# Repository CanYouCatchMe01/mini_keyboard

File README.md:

# Mini keyboard
I'm using this libray for the [Arduino Joystick Library](https://github.com/MHeironimus/ArduinoJoystickLibrary)
to emulate an controller. Then to emulate an XBOX 360 controller I use the [x360ce](https://github.com/x360ce/x360ce) application.

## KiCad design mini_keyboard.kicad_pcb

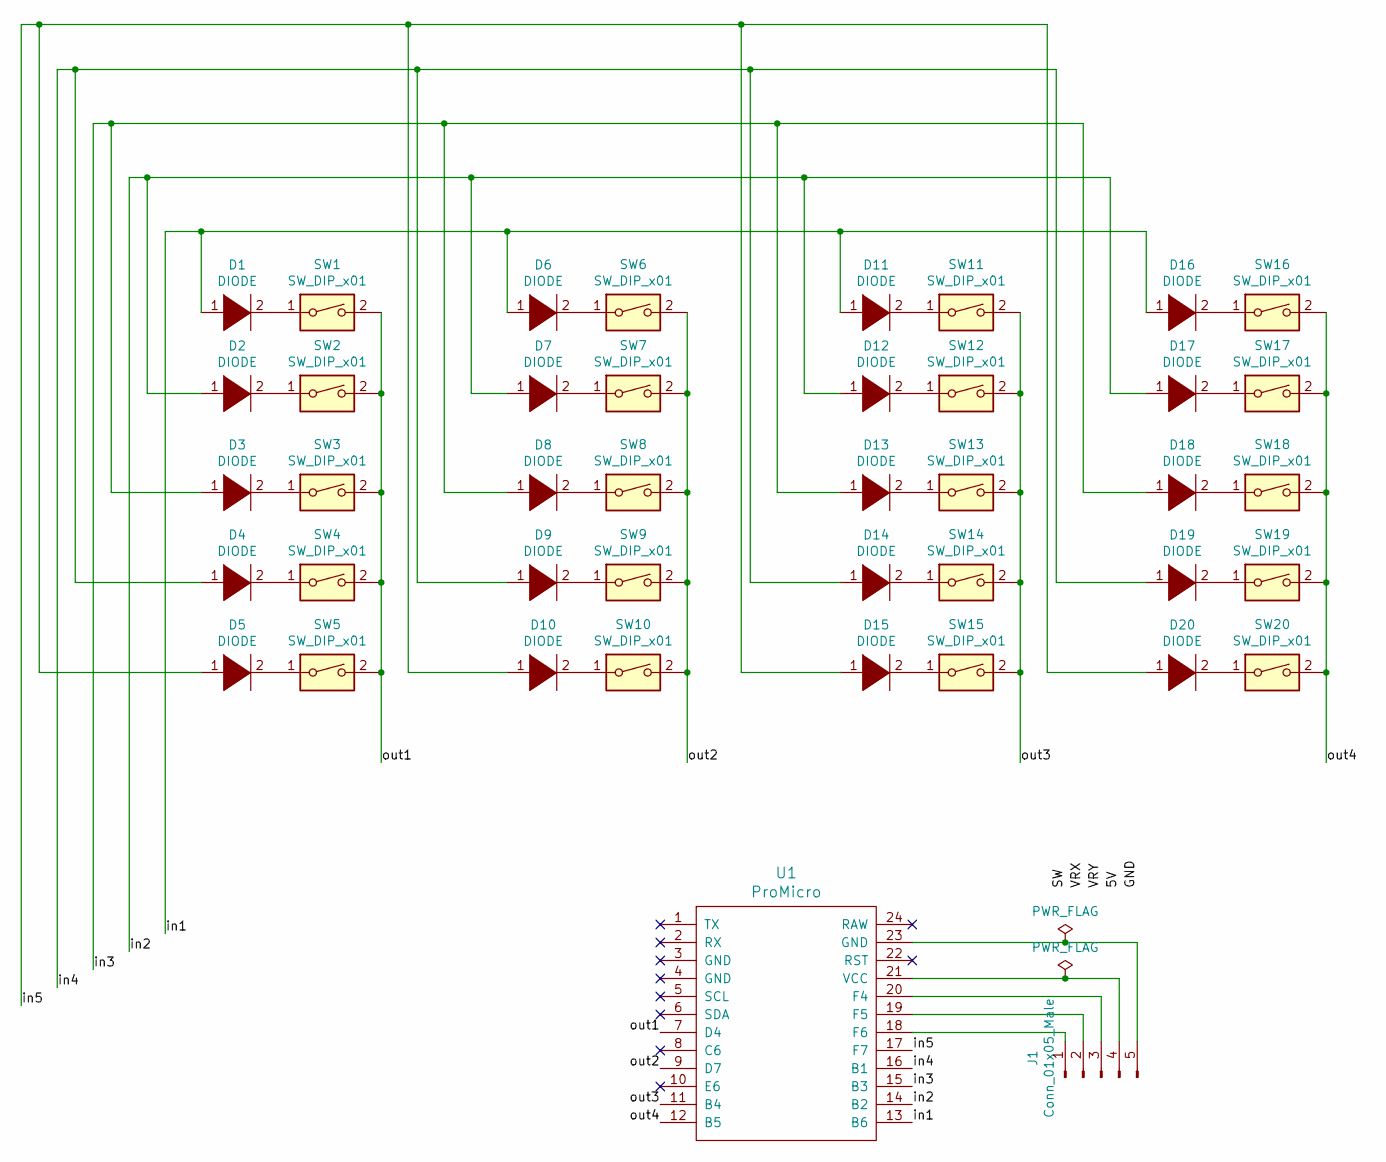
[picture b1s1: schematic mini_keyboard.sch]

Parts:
D1, D2, D3, D4, D5, D6, D7, D8, D9, D10, D11, D12, D13, D14, D15, D16, D17, D18, D19, D20: DIODE; D_T-1_P5.08mm_Horizontal
J1: Conn_01x05_Male; PinHeader_1x05_P2.54mm_Vertical
SW1, SW2, SW3, SW4, SW5, SW6, SW7, SW8, SW9, SW10, SW11, SW12, SW13, SW14, SW15, SW16, SW17, SW18, SW19, SW20: SW_DIP_x01; SW_Cherry_MX_1.00u_Plate
U1: ProMicro

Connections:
/in1: D1.1 (K), D6.1 (K), D11.1 (K), D16.1 (K), U1.13 (B6)
/in2: D2.1 (K), D7.1 (K), D12.1 (K), D17.1 (K), U1.14 (B2)
/in3: D3.1 (K), D8.1 (K), D13.1 (K), D18.1 (K), U1.15 (B3)
/in4: D4.1 (K), D9.1 (K), D14.1 (K), D19.1 (K), U1.16 (B1)
/in5: D5.1 (K), D10.1 (K), D15.1 (K), D20.1 (K), U1.17 (F7)
/out1: SW1.2, SW2.2, SW3.2, SW4.2, SW5.2, U1.7 (D4)
/out2: SW6.2, SW7.2, SW8.2, SW9.2, SW10.2, U1.9 (D7)
/out3: SW11.2, SW12.2, SW13.2, SW14.2, SW15.2, U1.11 (B4)
/out4: SW16.2, SW17.2, SW18.2, SW19.2, SW20.2, U1.12 (B5)
unnamed: D1.2 (A), SW1.1
unnamed: D2.2 (A), SW2.1
unnamed: D3.2 (A), SW3.1
unnamed: D4.2 (A), SW4.1
unnamed: D5.2 (A), SW5.1
unnamed: D6.2 (A), SW6.1
unnamed: D7.2 (A), SW7.1
unnamed: D8.2 (A), SW8.1
unnamed: D9.2 (A), SW9.1
unnamed: D10.2 (A), SW10.1
unnamed: D11.2 (A), SW11.1
unnamed: D12.2 (A), SW12.1
unnamed: D13.2 (A), SW13.1
unnamed: D14.2 (A), SW14.1
unnamed: D15.2 (A), SW15.1
unnamed: D16.2 (A), SW16.1
unnamed: D17.2 (A), SW17.1
unnamed: D18.2 (A), SW18.1
unnamed: D19.2 (A), SW19.1
unnamed: D20.2 (A), SW20.1
unnamed: J1.1, U1.18 (F6)
unnamed: J1.2, U1.19 (F5)
unnamed: J1.3, U1.20 (F4)
unnamed: J1.4, U1.21 (VCC)
unnamed: J1.5, U1.23 (GND)

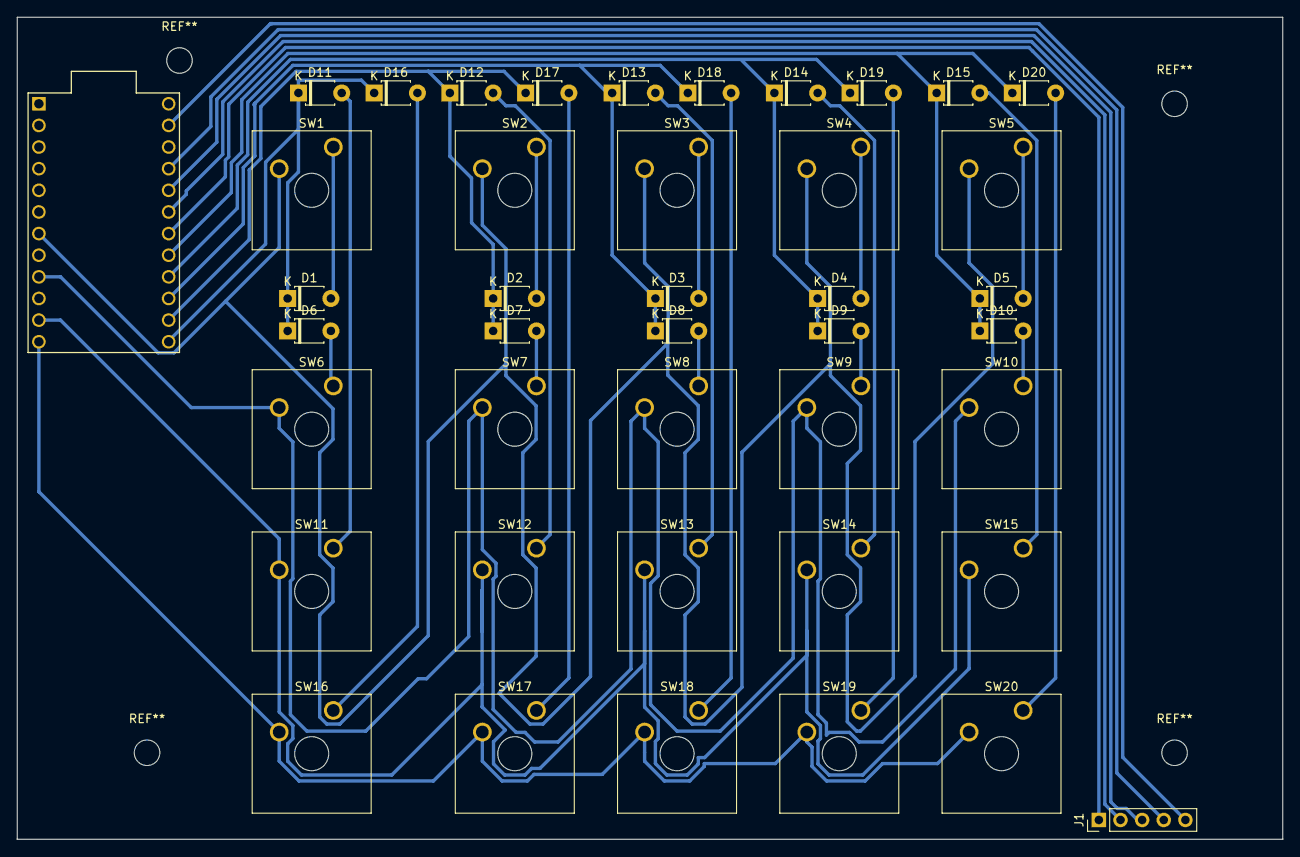
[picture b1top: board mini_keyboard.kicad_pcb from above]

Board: 2 copper layers, 148.6 x 96.5 mm, 42 parts (0 on the bottom side), 34 nets.

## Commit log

2020-12-12 Initial commit. Arduino micro + one charry MX switch
2020-12-12 updated git ignore
2020-12-12 .gitignore is now working
2020-12-12 Added all components
2020-12-14 Added 16 buttons, need 4 more
2020-12-14 added 20 buttons
2020-12-14 added joystick
2020-12-14 Mad joystick footprint, getting errors in lib editor
2021-01-25 PCB ready, no cables
2021-01-25 Moved buttons and made some lines
    Problem: Some cables are crossing
2021-01-25 gjort så många kablar som jag kan
    Nästa steg är att göra kablar som hoppar på undersidan
2021-01-29 pro micro + pin for joystick
2021-01-29 Added portal connections joystick
2021-01-29 rules check passed
2021-01-30 promicro footprint correct added
2021-01-30 made back and front cables
2021-01-30 moved joystick up
2021-02-01 no cables
2021-02-01 Thick lines
2021-02-01 Made out on right A_ ports
2021-02-02 removed ascii keyboard
2021-02-12 Made edge smaller
2021-02-13 made some design rules changes
2021-02-15 Update netlist. Wider left side
2021-02-15 clearance 0.3 Lines pressed at top
2021-02-15 lines done
2021-02-15 minor edit
2021-02-15 minor change2
2021-02-19 Moved holes a bit
2021-02-19 No extra cables
2021-02-19 Cleaned up no cables
2021-03-17 B.Cu as main layer. red swapped to green
2021-04-23 first code commit
2021-04-26 added test script
    to test if arduino is correct
2021-05-03 made input pulldown and simplified script
2021-06-08 working to debug the controller
2021-06-08 digital test script
2021-06-08 printing what button number is pressed
2021-06-08 Switch class, but still turning on
2021-06-09 controller working
2021-06-22 Mouse click on keyboard
2023-02-17 No mouse
2023-02-17 Moved the Kicad files to a new folder
2023-02-17 Removed the test script
2023-02-17 Added an README
